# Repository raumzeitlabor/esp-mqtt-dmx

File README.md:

# esp-mqtt-dmx 

This project is providing a MQTT-to-DMX gateway via an ESP8266 in our Hackerspace.
We used Artnet before but that just spams our network too much so this shall create some MQTT messages which control generic light setups like "fade all to white" or "fade Lamp 1 to red"

The ESP subscribes to topic "/dmx/push" on our MQTT broker and expects commands which we will describe here.

status: DRAFT

License: GPLv3

## MQTT-Commands

supported format of commands to be published to the "/dmx/push" topic:

|command|parameters|description|
|-------|----------|-----------|
|blackout|none|instantly set all values to 0 thus switching all lamps off|
|fadespeed|speed in miliseconds|this value is used as a "step width" to move from current DMX state to desired DMX state. Default value = 20, values below 20 seem to produce weird effects!|
|fadealltoblack|none|set all desired rgbl values for all light to 0 and fade towards that (darkness)|
|fadealltowhite|none|set all desired rgbl values for all light to 255 and fade towards that ("white")|
|fadealltored|none|set all desired rgbl values for all light to fade towards red|
|fadealltogreen|none|set all desired rgbl values for all light to fade towards green|
|fadealltoblue|none|set all desired rgbl values for all light to fade towards blue|
|cycleallrandom|brightness|set a random value (and optionally a brightness) for all rgbl values for all lights and fade towards that value|
|cyclerandom|light brightness|set a specific light to random rgbl values (and optionally a brightness) and fade towards them (index starts at 0)|
|rgbl|light R G B L|set a specific light to specific values for R G B L (values 0-255)|
|setchannel|channel value|set a specific DMX channel to one specific value (without fading, hard set)|
|discopanic|none|set all lights to a random color strobe (using a special DMX channel/value pair)|
|fadeRGB|none|set all lights to go through a slow cycle of colors (using a special DMX channel/value pair)|
|strobo|speed intensity|activate the strobo (speed and intesity optional 0-255, both 255 if no options provided)|

## Compiler config

We use an ESP-12E Module with 4M Flash-Size and 3M SPIFFS. This is important for in order to be able to do Web-OTA Updates we need the 3M SPIFFS to fit two versions of the Firmware into memory. Using 4M-1M Split will crash the controller during OTA. If using Arduino-IDE set Board to "NodeMCU 1.0 (ESP-12E Module)" and Flash to "4M (3M SPIFFS)"

At the time of writing (02/2019) the Arduino-Board-Version v4.2 seems to work well.

## OTA

compile with Arduino ide and upload via curl because we don't use mdns announce:

    curl -F "image=@esp-mqtt-dmx.ino.nodemcu.bin" http://172.22.37.112/update

## Websocket-Server

we run a websocket server on port 81 which prints some messages for debugging (because we're lazy and don't want to use the UART all the time).

## Credits

The main libraries/sources of code are:
  - espDMX written by Matt (@mtongnz), https://github.com/mtongnz/espDMX
  - esp ArtnetNode by Matt (@mtongnz), https://github.com/mtongnz/ESP8266_ArtNetNode_DMX
  - ESP8266 core for Arduino, https://github.com/esp8266/Arduino

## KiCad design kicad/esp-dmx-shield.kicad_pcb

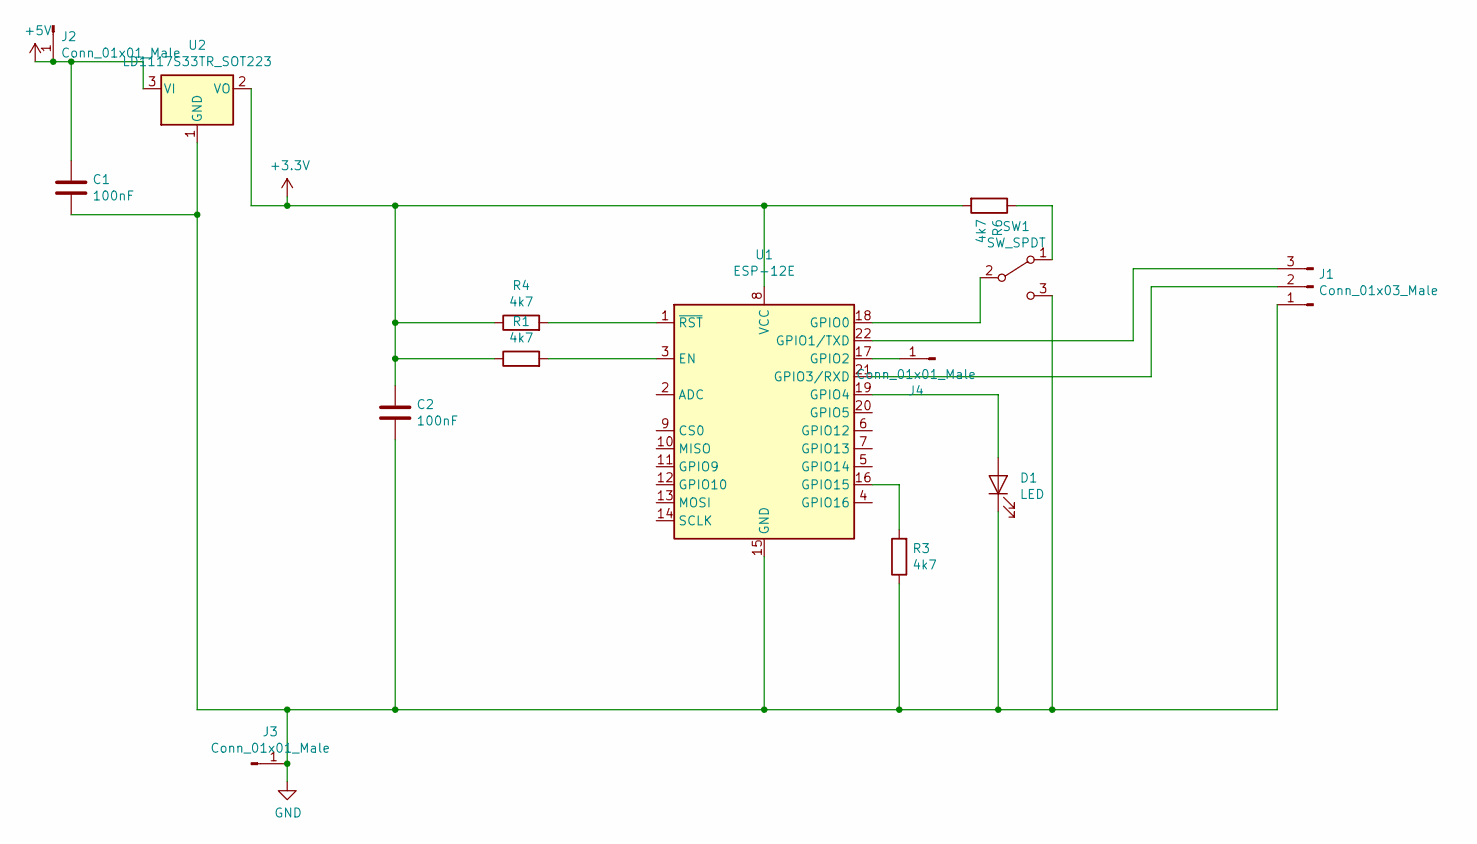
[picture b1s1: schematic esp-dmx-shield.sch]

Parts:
C1, C2: 100nF; C_1206_3216Metric_Pad1.42x1.75mm_HandSolder
D1: LED; SolderJumper-2_P1.3mm_Open_Pad1.0x1.5mm
J1: Conn_01x03_Male; SolderJumper-3_P1.3mm_Open_Pad1.0x1.5mm_NumberLabels
J2, J3, J4: Conn_01x01_Male; SolderWirePad_1x01_Drill0.8mm
R1, R3, R4, R6: 4k7; R_1206_3216Metric_Pad1.42x1.75mm_HandSolder
SW1: SW_SPDT; SolderJumper-3_P1.3mm_Open_Pad1.0x1.5mm
U1: ESP-12E
U2: LD1117S33TR_SOT223; TO-220-3_Vertical

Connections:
+3V3: C2.1, R1.1, R4.1, R6.2, U1.8 (VCC), U2.2 (VO)
+5V: C1.1, J2.1, U2.3 (VI)
GND: C1.2, C2.2, D1.1 (K), J1.1, J3.1, R3.1, SW1.3 (C), U1.15 (GND), U2.1 (GND)
unnamed: D1.2 (A), U1.19 (GPIO4)
unnamed: J1.2, U1.21 (GPIO3/RXD)
unnamed: J1.3, U1.22 (GPIO1/TXD)
unnamed: J4.1, U1.17 (GPIO2)
unnamed: R1.2, U1.3 (EN)
unnamed: R3.2, U1.16 (GPIO15)
unnamed: R4.2, U1.1 (~RST)
unnamed: R6.1, SW1.1 (A)
unnamed: SW1.2 (B), U1.18 (GPIO0)

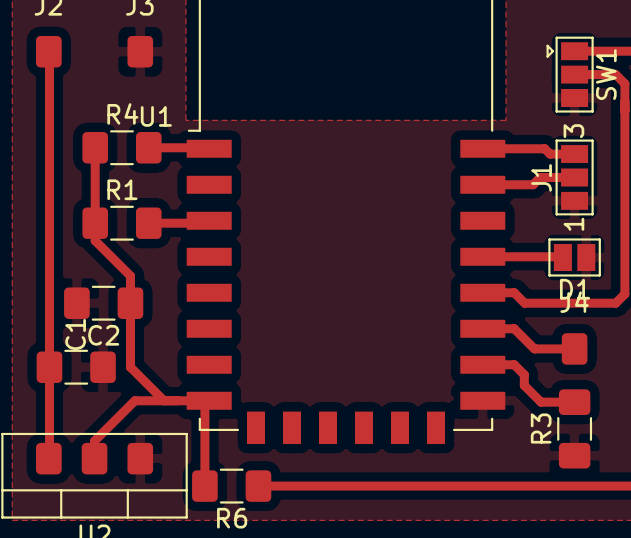
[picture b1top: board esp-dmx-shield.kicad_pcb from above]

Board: 2 copper layers, 14 parts (0 on the bottom side), 12 nets.

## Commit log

2019-02-02 initial import
2019-02-02 implement fadetoblack and fadetowhite mqtt messages
2019-02-02 corrected fadetowhite and introduced cyclerandom
2019-02-02 typo fix and make fade quicker
2019-02-02 random repaired, rgbl command implemented
2019-02-02 changed topic to dmx, added setchannel function
2019-02-04 new functions, better fadespeed, using all lamps...
2019-02-04 added current supported commands
2019-02-04 ignore vscode
2019-02-04 pull out led pin variable
2019-02-04 add compile and ota info to readme
2019-02-04 add some debug messages.
2019-02-04 websocket server to readme.
2019-02-05 Create LICENSE
2019-02-05 change license and add credits
2019-02-17 better handling, new commands, nicer fading
2019-02-17 update commands table
2019-02-20 beautified and added new command for strobe
2019-02-20 add new command to readme
2019-02-20 Travis (#4)
    * try travis
    * typo :-(
    * dont need
    * another try
    * now?
    * now?
2019-02-20 add the travis-bling :-)
